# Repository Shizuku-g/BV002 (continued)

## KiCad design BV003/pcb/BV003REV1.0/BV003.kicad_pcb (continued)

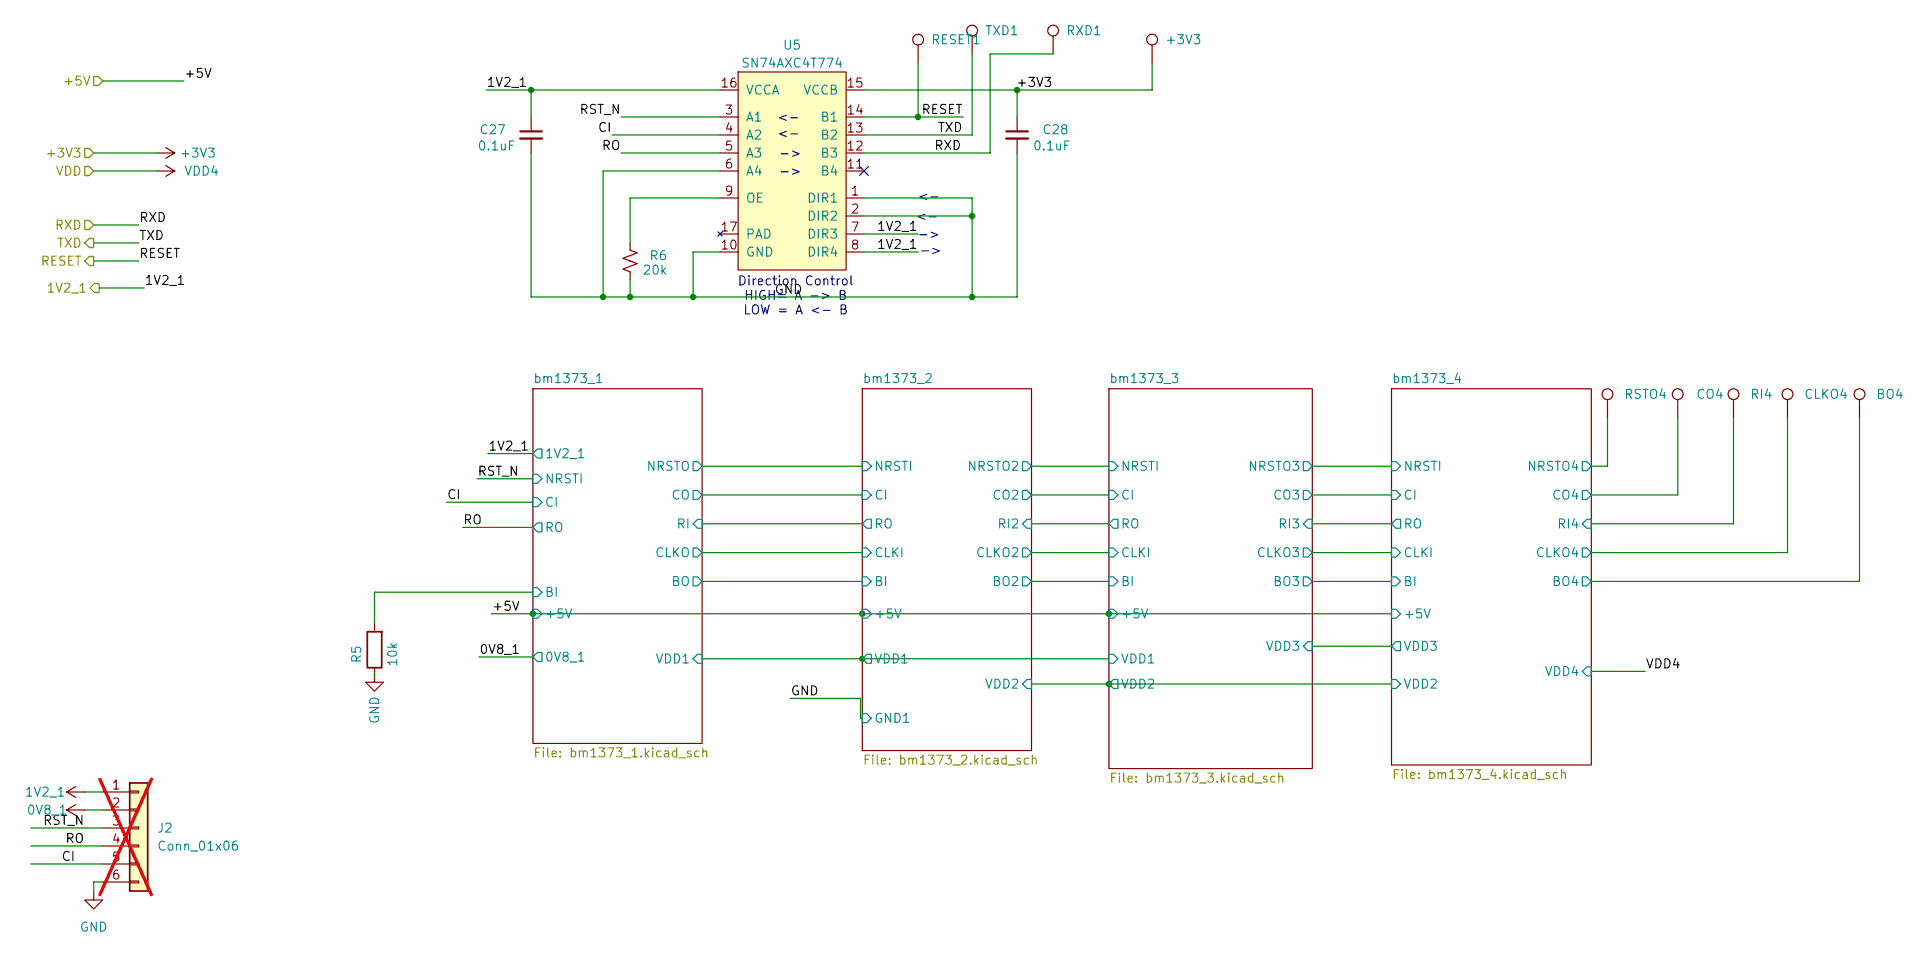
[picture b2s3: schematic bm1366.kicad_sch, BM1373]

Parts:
+3V3: TestPoint_Pad_D1.5mm
BO4: TestPoint_Pad_D1.5mm
C27, C28: 0.1uF; C_0402_1005Metric; PARTNO KGM05AR71C104KH
CLKO4: TestPoint_Pad_D1.5mm
CO4: TestPoint_Pad_D1.5mm
J2: Conn_01x06; PinHeader_1x06_P1.27mm_Vertical; not fitted
R5: 10k; R_0402_1005Metric; LCSC C140868
R6: 20k; R_0402_1005Metric; PARTNO RC0402FR-0720KL
RESET1: TestPoint_Pad_D1.5mm
RI4: TestPoint_Pad_D1.5mm
RSTO4: TestPoint_Pad_D1.5mm
RXD1: TestPoint_Pad_D1.5mm
TXD1: TestPoint_Pad_D1.5mm
U5: SN74AXC4T774; TSSOP-16_4.4x5mm_P0.65mm; PARTNO SN74AXC4T774BQBR

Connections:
1V2_1: C27.1, J2.1, U5.7 (DIR3), U5.8 (DIR4), U5.16 (VCCA); also elsewhere on the board
+0V8_1: J2.2; also elsewhere on the board
+3V3: +3V3.1 (1_1), C28.1, U5.15 (VCCB); also elsewhere on the board
/BM1370/CI: J2.5, U5.4 (A2); also elsewhere on the board
/BM1370/RESET: RESET1.1 (1_1), U5.14 (B1); also elsewhere on the board
/BM1370/RO: J2.4, U5.5 (A3); also elsewhere on the board
/BM1370/RST_N: J2.3, U5.3 (A1); also elsewhere on the board
/BM1370/RXD: RXD1.1 (1_1), U5.12 (B3); also elsewhere on the board
/BM1370/TXD: TXD1.1 (1_1), U5.13 (B2); also elsewhere on the board
/BM1370/bm1373_1/BI: R5.2; also elsewhere on the board
/BM1370/bm1373_4/BO: BO4.1 (1_1); also elsewhere on the board
/BM1370/bm1373_4/CLKO4: CLKO4.1 (1_1); also elsewhere on the board
/BM1370/bm1373_4/CO: CO4.1 (1_1); also elsewhere on the board
/BM1370/bm1373_4/RI: RI4.1 (1_1); also elsewhere on the board
/BM1370/bm1373_4/RSTO: RSTO4.1 (1_1); also elsewhere on the board
GND: C27.2, C28.2, J2.6, R5.1, R6.1, U5.1 (DIR1), U5.2 (DIR2), U5.6 (A4), U5.10 (GND); also elsewhere on the board
unnamed: R6.2, U5.9 (OE)

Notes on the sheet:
Direction Control HIGH= A -> B LOW = A <- B

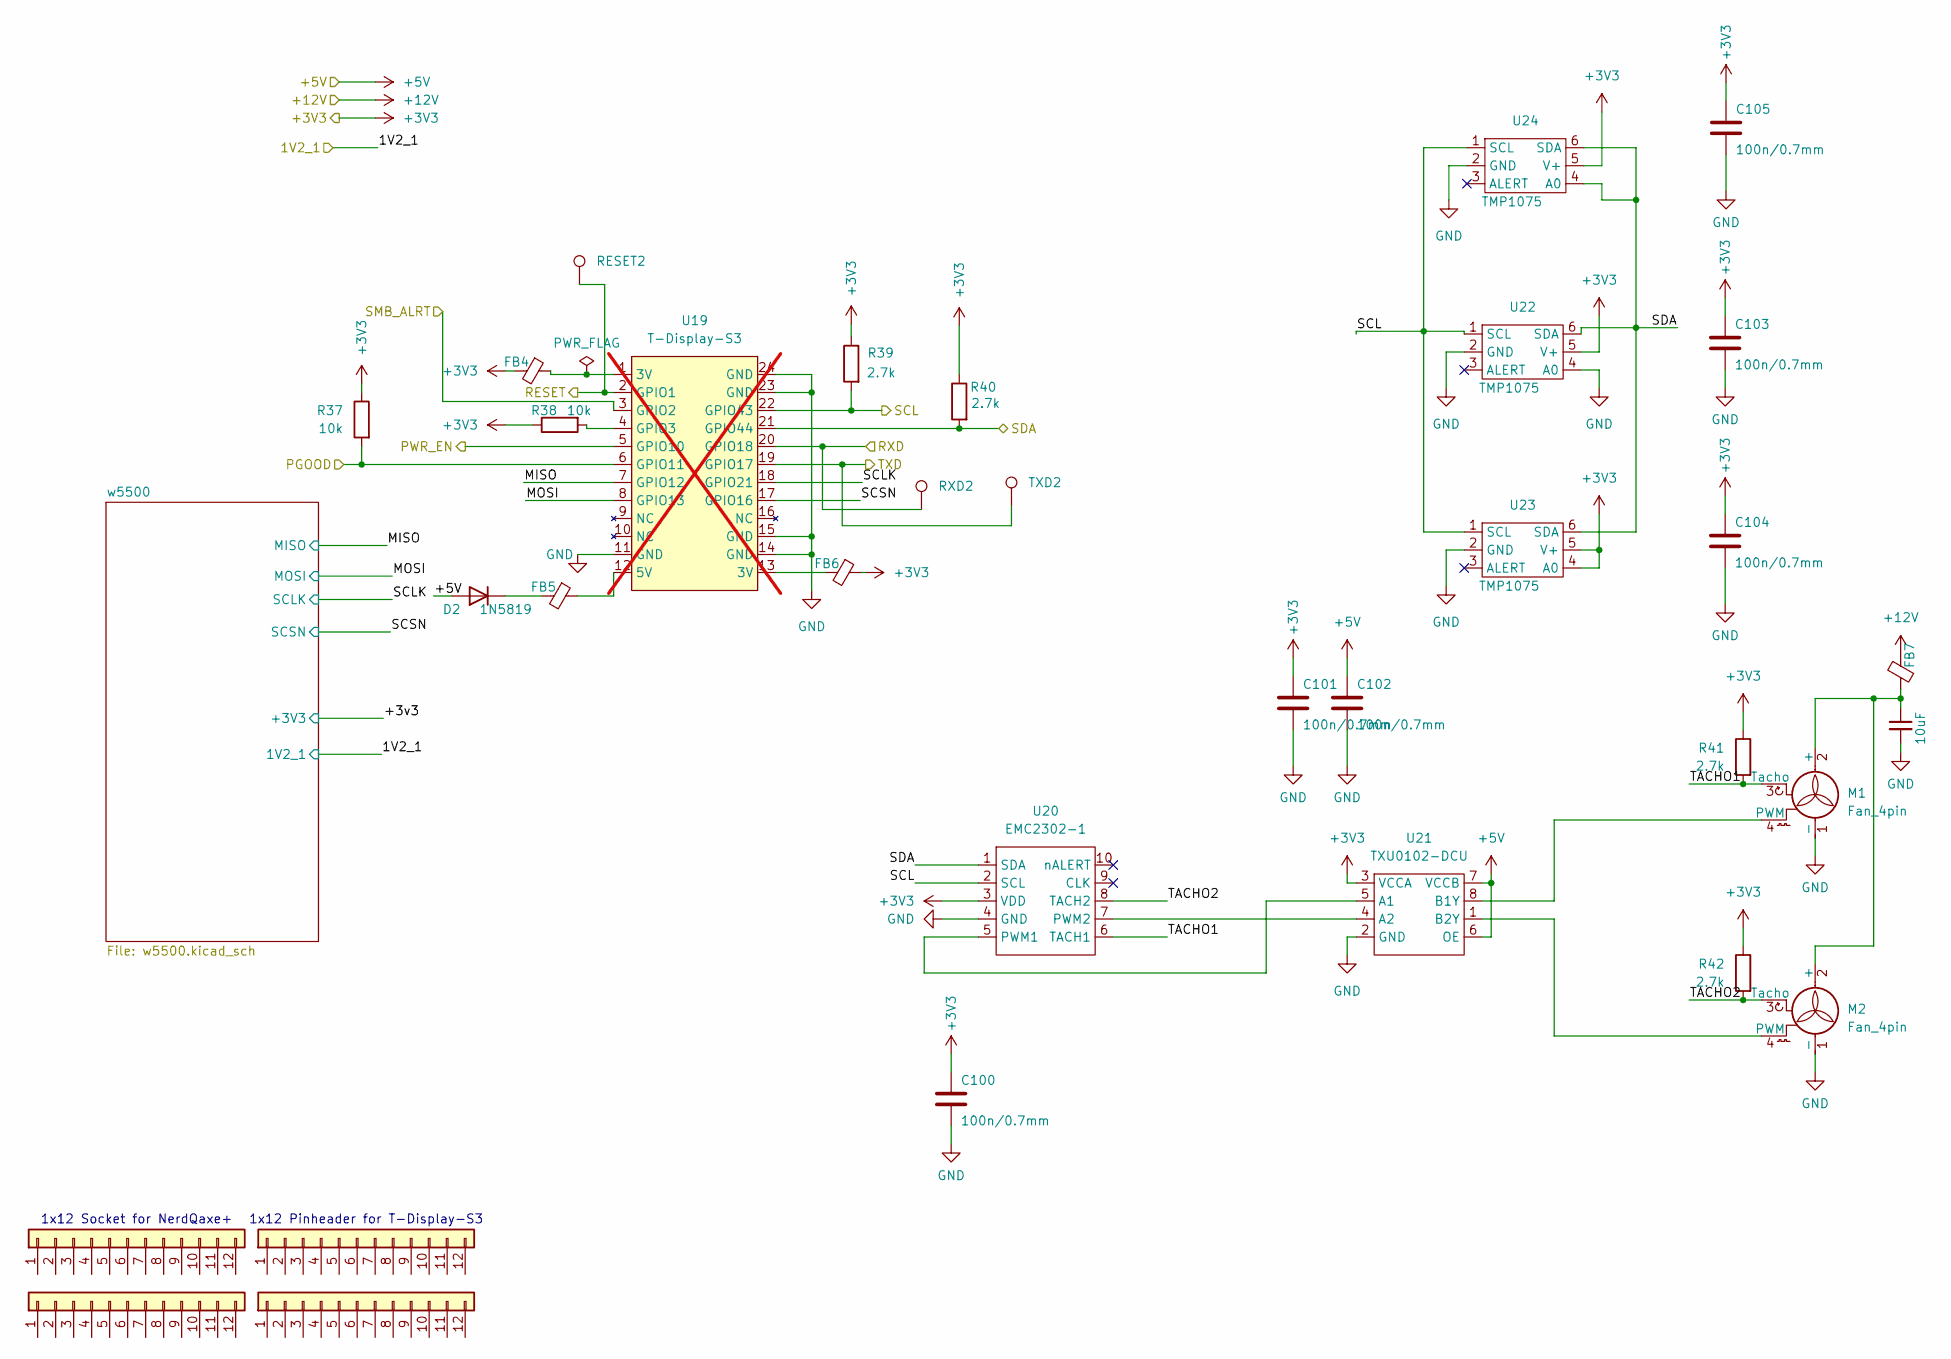
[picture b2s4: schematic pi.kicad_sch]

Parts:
C100, C101, C102, C103, C104, C105: 100n/0.7mm; C_0805_2012Metric; LCSC C519981
C106: 10uF; C_0603_1608Metric; PARTNO CL10A106MO8NQNC; LCSC C92487
D2: 1N5819; D_SMA; PARTNO C460770; LCSC C460770
FB4, FB5, FB6, FB7: BLM21PG221SN1D; R_0805_2012Metric; LCSC C85840
J3, J4: Conn_01x12-Socket
J5, J6: Conn_01x12-Header
M1, M2: Fan_4pin; FanPinHeader_1x04_P2.54mm_Vertical; LCSC C240840
R37, R38: 10k; R_0805_2012Metric; LCSC C140868
R39, R40, R41, R42: 2.7k; R_0805_2012Metric; LCSC C17530
RESET2: TestPoint_Pad_D1.5mm
RXD2: TestPoint_Pad_D1.5mm
TXD2: TestPoint_Pad_D1.5mm
U19: T-Display-S3; not fitted
U20: EMC2302-1; MSOP-10_3x3mm_P0.5mm; LCSC C626969
U21: TXU0102-DCU; VSSOP-8_2.3x2mm_P0.5mm; LCSC C5217871
U22, U23, U24: TMP1075; TMP1075-DRL; LCSC C3663690

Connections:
+3V3: C100.1, C101.1, C103.1, C104.1, C105.1, FB4.2, FB6.1, R37.1, R38.1, R39.1, R40.1, R40.2, R41.1, R42.1, U19.21 (GPIO44), U20.1 (SDA), U20.3 (VDD), U21.3 (VCCA), U22.5 (V+), U22.6 (SDA), U23.4 (A0), U23.5 (V+), U23.6 (SDA), U24.4 (A0), U24.5 (V+), U24.6 (SDA); also elsewhere on the board
+5V: C102.1, D2.2 (A), U21.6 (OE), U21.7 (VCCB); also elsewhere on the board
/BM1370/RESET: RESET2.1 (1_1), U19.2 (GPIO1); also elsewhere on the board
/BM1370/RXD: RXD2.1 (1_1), U19.20 (GPIO18); also elsewhere on the board
/BM1370/TXD: TXD2.1 (1_1), U19.19 (GPIO17); also elsewhere on the board
/T-Display-S3/MISO: U19.7 (GPIO12); also elsewhere on the board
/T-Display-S3/MOSI: U19.8 (GPIO13); also elsewhere on the board
/T-Display-S3/SCL: R39.2, U19.22 (GPIO43), U20.2 (SCL), U22.1 (SCL), U23.1 (SCL), U24.1 (SCL); also elsewhere on the board
/T-Display-S3/SCLK: U19.18 (GPIO21); also elsewhere on the board
/T-Display-S3/SCSN: U19.17 (GPIO16); also elsewhere on the board
/T-Display-S3/SMB_ALRT: U19.3 (GPIO2); also elsewhere on the board
/T-Display-S3/TACHO1: M1.3 (Tacho), R41.2, U20.6 (TACH1)
/T-Display-S3/TACHO2: M2.3 (Tacho), R42.2, U20.8 (TACH2)
/power1/PWR_EN: U19.5 (GPIO10); also elsewhere on the board
GND: C100.2, C101.2, C102.2, C103.2, C104.2, C105.2, C106.2, M1.1 (-), M2.1 (-), U19.11 (GND), U19.14 (GND), U19.15 (GND), U19.23 (GND), U19.24 (GND), U20.4 (GND), U21.2 (GND), U22.2 (GND), U22.4 (A0), U23.2 (GND), U24.2 (GND); also elsewhere on the board
unnamed: D2.1 (K), FB5.2
unnamed: FB4.1, U19.1 (3V)
unnamed: FB6.2, U19.13 (3V)
unnamed: C106.1, FB7.1, M1.2 (+), M2.2 (+)
unnamed: M1.4 (PWM), U21.8 (B1Y)
unnamed: M2.4 (PWM), U21.1 (B2Y)
unnamed: FB5.1, U19.12 (5V)
unnamed: R38.2, U19.4 (GPIO3)
unnamed: U20.5 (PWM1), U21.5 (A1)
unnamed: U20.7 (PWM2), U21.4 (A2)
PGOOD: R37.2, U19.6 (GPIO11); also elsewhere on the board

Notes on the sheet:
1x12 Socket for NerdQaxe+
1x12 Pinheader for T-Display-S3

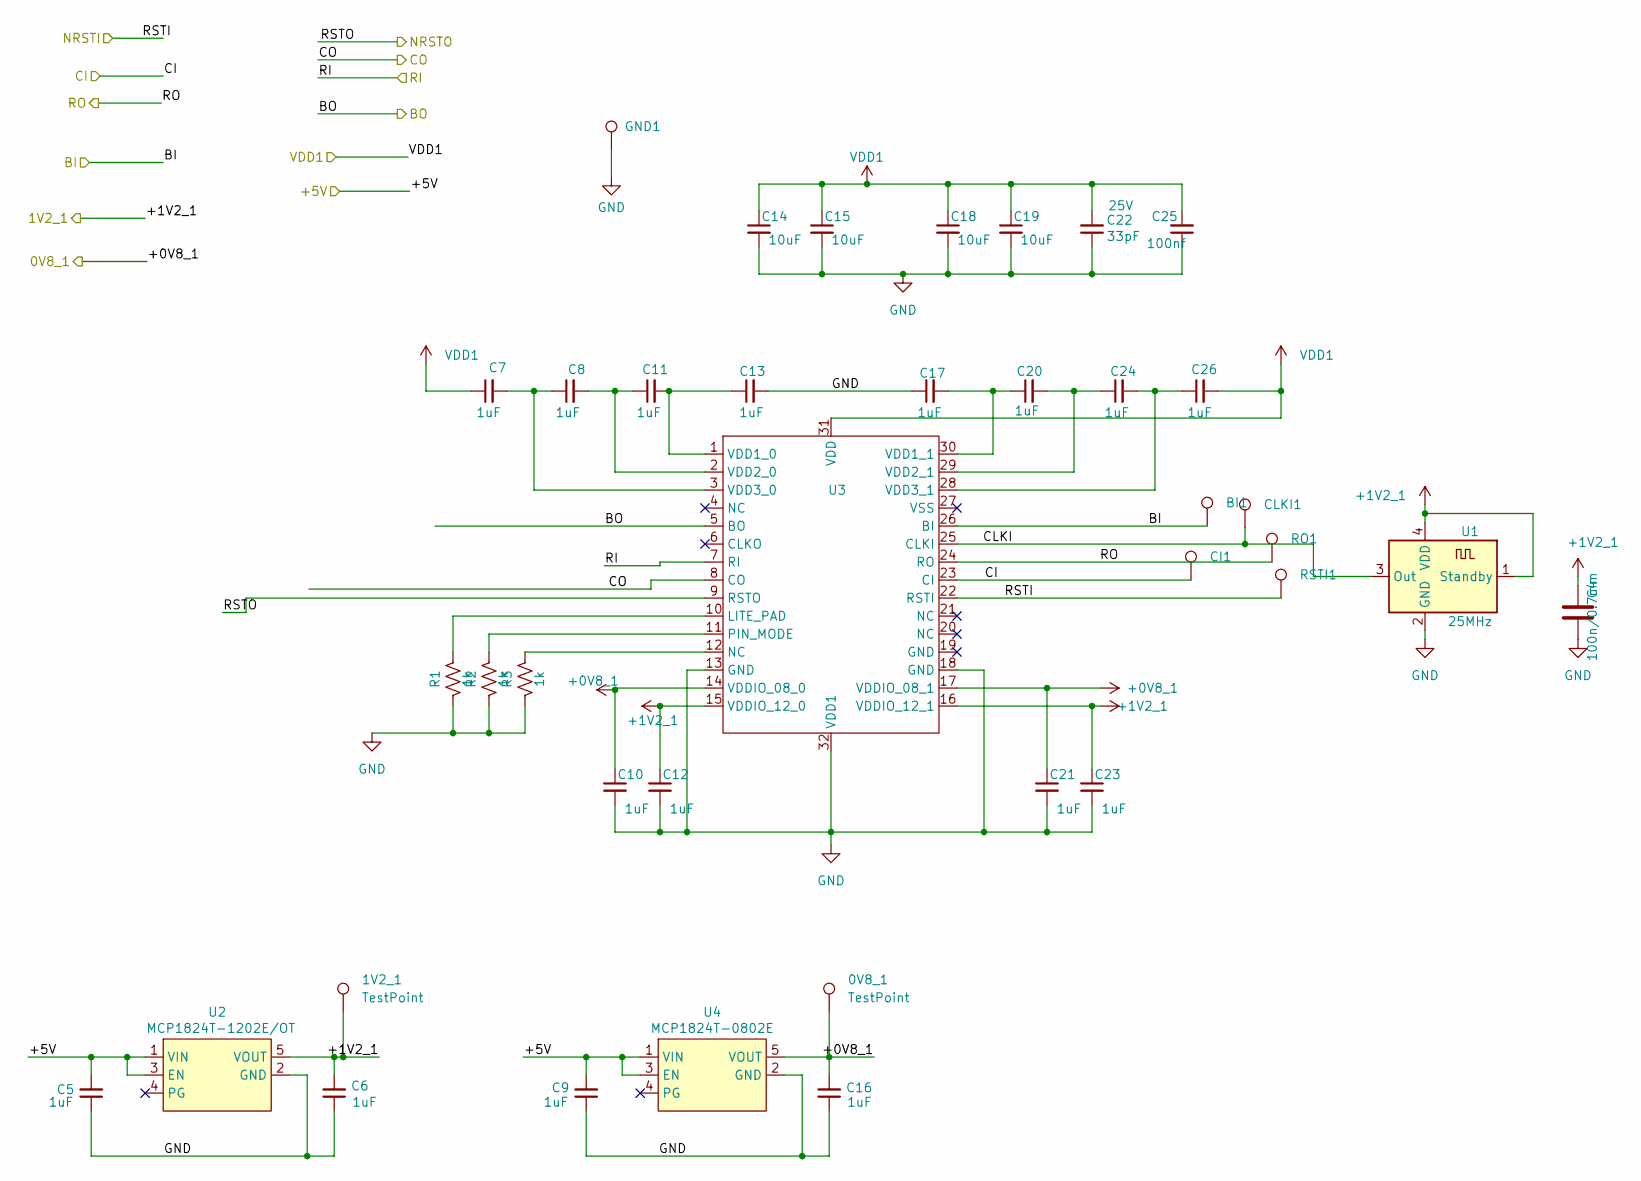
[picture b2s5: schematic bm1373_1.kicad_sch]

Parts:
0V8_1, 1V2_1: TestPoint; TestPoint_Pad_D1.5mm
BI1: TestPoint_Pad_D1.5mm
C4: 100n/0.7mm; C_0805_2012Metric; LCSC C519981
C5, C6, C9, C16: 1uF; C_0402_1005Metric; PARTNO EMK105BJ105MV-F
C7, C8, C10, C11, C12, C13, C17, C20, C21, C23, C24, C26: 1uF; C_0402_1005Metric; PARTNO CL05A105KO5NNNC; LCSC C29266
C14, C15, C18, C19: 10uF; C_0603_1608Metric; PARTNO CL10A106MO8NQNC; LCSC C92487 Hot
C22: 33pF; C_0402_1005Metric; Voltage 25V; PARTNO KGM05ACG1E330JH
C25: 100nf; C_0402_1005Metric; PARTNO GRM188R61E106KA73D
CI1: TestPoint_Pad_D1.5mm
CLKI1: TestPoint_Pad_D1.5mm
GND1: TestPoint_Pad_D1.5mm
R1, R2, R3: 1k; R_0402_1005Metric; PARTNO RC0402FR-071KL; LCSC C106235
RO1: TestPoint_Pad_D1.5mm
RSTI1: TestPoint_Pad_D1.5mm
U1: 25MHz; Oscillator_SMD_Abracon_ASDMB-4Pin_2.5x2.0mm; LCSC C5137262
U2: MCP1824T-1202E/OT; SOT-23-5; PARTNO MCP1824T-1202E/OT
U3: B1373CC
U4: MCP1824T-0802E; SOT-23-5; PARTNO MCP1824T-0802E/OT

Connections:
1V2_1: 1V2_1.1 (1_1), C4.1, C6.2, C12.1, C23.1, U1.1 (Standby), U1.4 (VDD), U2.5 (VOUT), U3.15 (VDDIO_12_0), U3.16 (VDDIO_12_1); also elsewhere on the board
+0V8_1: 0V8_1.1 (1_1), C10.1, C16.2, C21.1, U3.14 (VDDIO_08_0), U3.17 (VDDIO_08_1), U4.5 (VOUT); also elsewhere on the board
+5V: C5.2, C9.2, U2.1 (VIN), U2.3 (EN), U4.1 (VIN), U4.3 (EN); also elsewhere on the board
/BM1370/CI: CI1.1 (1_1), U3.23 (CI); also elsewhere on the board
/BM1370/RO: RO1.1 (1_1), U3.24 (RO); also elsewhere on the board
/BM1370/RST_N: RSTI1.1 (1_1), U3.22 (RSTI); also elsewhere on the board
/BM1370/bm1373_1/BI: BI1.1 (1_1), U3.26 (BI); also elsewhere on the board
/BM1370/bm1373_1/BO: U3.5 (BO); also elsewhere on the board
/BM1370/bm1373_1/CLKI: CLKI1.1 (1_1), U1.3 (Out), U3.25 (CLKI)
/BM1370/bm1373_1/CO: U3.8 (CO); also elsewhere on the board
/BM1370/bm1373_1/RI: U3.7 (RI); also elsewhere on the board
/BM1370/bm1373_1/RSTO: U3.9 (RSTO); also elsewhere on the board
GND: C4.2, C5.1, C6.1, C9.1, C10.2, C12.2, C13.2, C14.2, C15.2, C16.1, C17.1, C18.2, C19.2, C21.2, C22.1, C23.2, C25.1, GND1.1 (1_1), R1.2, R2.2, R3.2, U1.2 (GND), U2.2 (GND), U3.13 (GND), U3.18 (GND), U3.19 (GND), U3.32 (VDD1), U4.2 (GND); also elsewhere on the board
unnamed: R3.1, U3.12 (NC)
unnamed 110: U3.6 (CLKO); also elsewhere on the board
unnamed: R1.1, U3.10 (LITE_PAD)
unnamed: R2.1, U3.11 (PIN_MODE)
unnamed: C11.2, C13.1, U3.1 (VDD1_0)
unnamed: C17.2, C20.1, U3.30 (VDD1_1)
unnamed: C8.2, C11.1, U3.2 (VDD2_0)
unnamed: C20.2, C24.1, U3.29 (VDD2_1)
unnamed: C7.2, C8.1, U3.3 (VDD3_0)
unnamed: C24.2, C26.1, U3.28 (VDD3_1)
VDD1: C7.1, C14.1, C15.1, C18.1, C19.1, C22.2, C25.2, C26.2, U3.31 (VDD); also elsewhere on the board

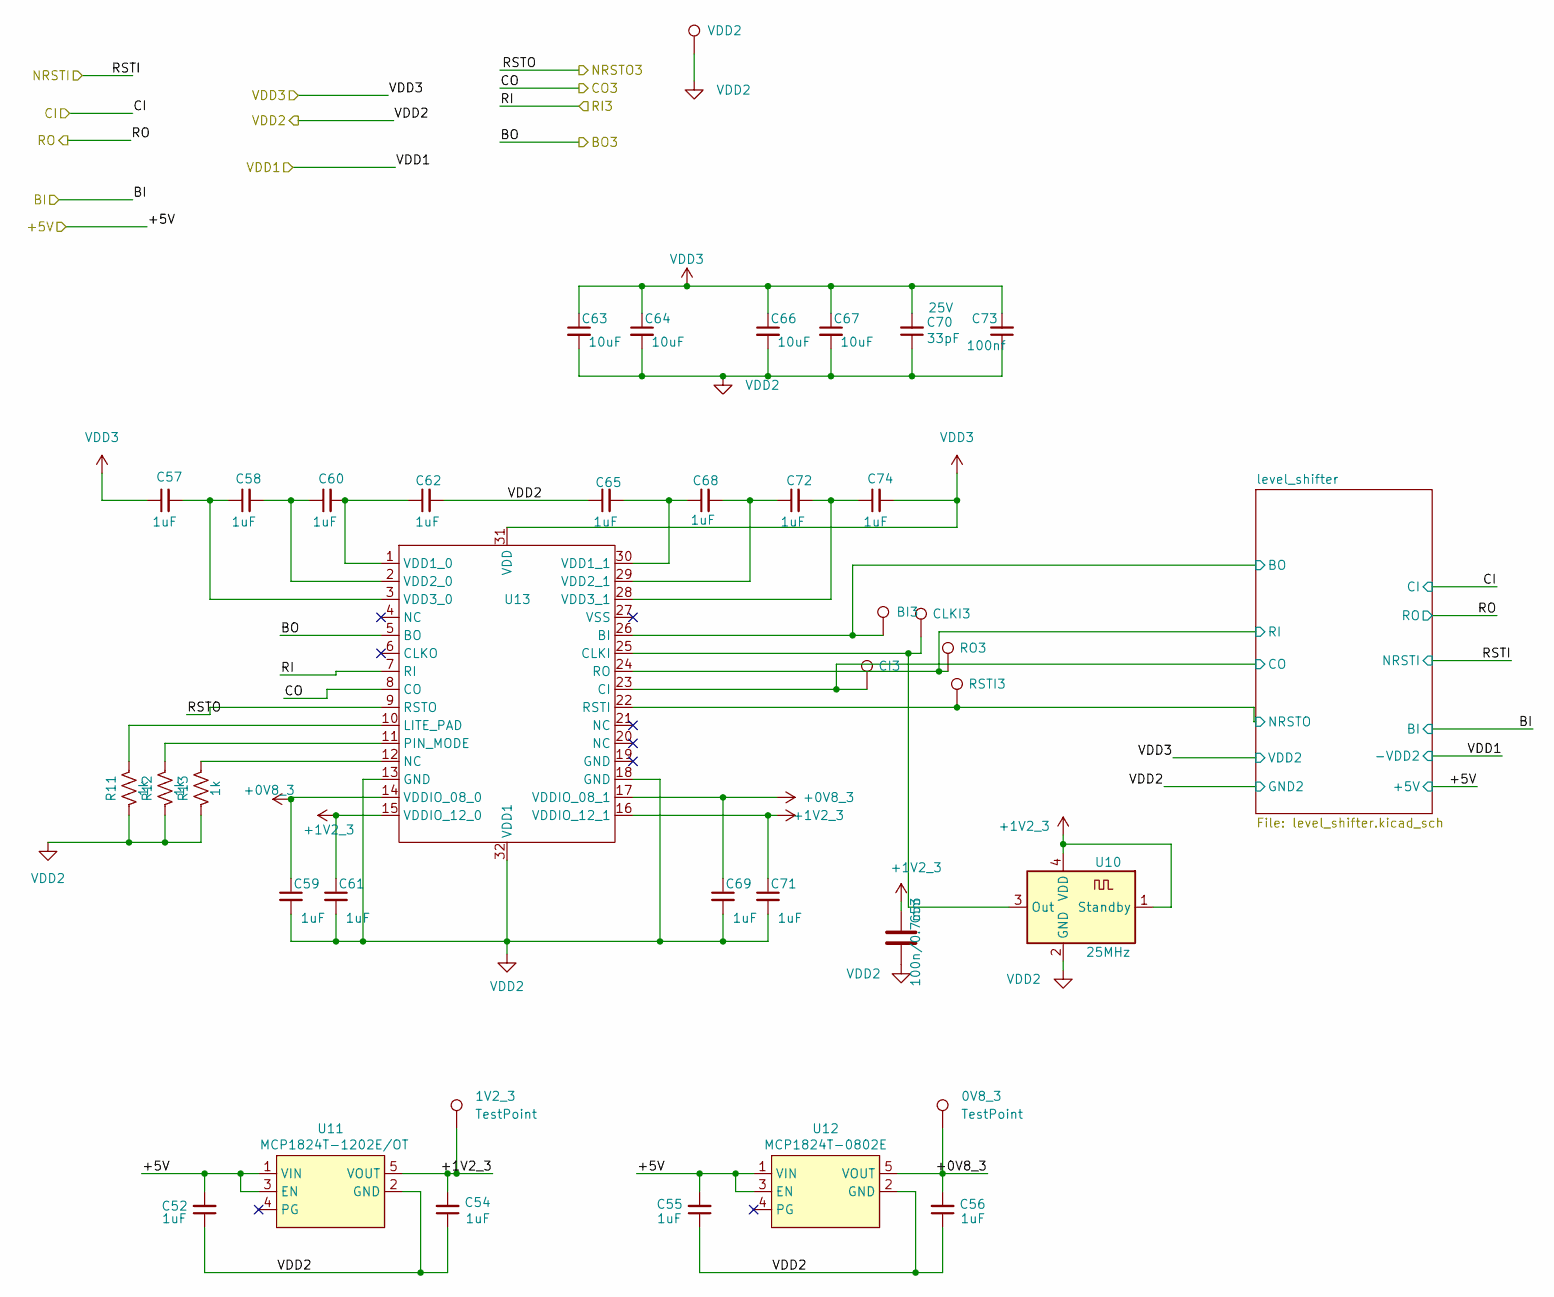
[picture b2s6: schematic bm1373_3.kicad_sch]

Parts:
0V8_3, 1V2_3: TestPoint; TestPoint_Pad_D1.5mm
BI3: TestPoint_Pad_D1.5mm
C52, C54, C55, C56: 1uF; C_0402_1005Metric; PARTNO EMK105BJ105MV-F
C53: 100n/0.7mm; C_0805_2012Metric; LCSC C519981
C57, C58, C59, C60, C61, C62, C65, C68, C69, C71, C72, C74: 1uF; C_0402_1005Metric; PARTNO CL05A105KO5NNNC; LCSC C29266
C63, C64, C66, C67: 10uF; C_0603_1608Metric; PARTNO CL10A106MO8NQNC; LCSC C92487 Hot
C70: 33pF; C_0402_1005Metric; Voltage 25V; PARTNO KGM05ACG1E330JH
C73: 100nf; C_0402_1005Metric; PARTNO GRM188R61E106KA73D
CI3: TestPoint_Pad_D1.5mm
CLKI3: TestPoint_Pad_D1.5mm
R11, R12, R13: 1k; R_0402_1005Metric; PARTNO RC0402FR-071KL; LCSC C106235
RO3: TestPoint_Pad_D1.5mm
RSTI3: TestPoint_Pad_D1.5mm
U10: 25MHz; Oscillator_SMD_Abracon_ASDMB-4Pin_2.5x2.0mm; LCSC C5137262
U11: MCP1824T-1202E/OT; SOT-23-5; PARTNO MCP1824T-1202E/OT
U12: MCP1824T-0802E; SOT-23-5; PARTNO MCP1824T-0802E/OT
U13: B1373CC
VDD2: TestPoint_Pad_D1.5mm

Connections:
+0V8_3: 0V8_3.1 (1_1), C56.2, C59.1, C69.1, U12.5 (VOUT), U13.14 (VDDIO_08_0), U13.17 (VDDIO_08_1)
+1V2_3: 1V2_3.1 (1_1), C53.1, C54.2, C61.1, C71.1, U10.1 (Standby), U10.4 (VDD), U11.5 (VOUT), U13.15 (VDDIO_12_0), U13.16 (VDDIO_12_1)
+5V: C52.2, C55.2, U11.1 (VIN), U11.3 (EN), U12.1 (VIN), U12.3 (EN); also elsewhere on the board
/BM1370/bm1373_3/BO: U13.5 (BO); also elsewhere on the board
/BM1370/bm1373_3/CO: U13.8 (CO); also elsewhere on the board
/BM1370/bm1373_3/RI: U13.7 (RI); also elsewhere on the board
/BM1370/bm1373_3/RSTO: U13.9 (RSTO); also elsewhere on the board
/BM1370/bm1373_3/level_shifter/BI2: BI3.1 (1_1), U13.26 (BI); also elsewhere on the board
/BM1370/bm1373_3/level_shifter/CI2: CI3.1 (1_1), U13.23 (CI); also elsewhere on the board
/BM1370/bm1373_3/level_shifter/NRSTI2: RSTI3.1 (1_1), U13.22 (RSTI); also elsewhere on the board
/BM1370/bm1373_3/level_shifter/RO2: RO3.1 (1_1), U13.24 (RO); also elsewhere on the board
unnamed: R13.1, U13.12 (NC)
unnamed: CLKI3.1 (1_1), U10.3 (Out), U13.25 (CLKI)
unnamed 131: U13.6 (CLKO); also elsewhere on the board
unnamed: R11.1, U13.10 (LITE_PAD)
unnamed: R12.1, U13.11 (PIN_MODE)
unnamed: C60.2, C62.1, U13.1 (VDD1_0)
unnamed: C65.2, C68.1, U13.30 (VDD1_1)
unnamed: C58.2, C60.1, U13.2 (VDD2_0)
unnamed: C68.2, C72.1, U13.29 (VDD2_1)
unnamed: C57.2, C58.1, U13.3 (VDD3_0)
unnamed: C72.2, C74.1, U13.28 (VDD3_1)
VDD2: C52.1, C53.2, C54.1, C55.1, C56.1, C59.2, C61.2, C62.2, C63.2, C64.2, C65.1, C66.2, C67.2, C69.2, C70.1, C71.2, C73.1, R11.2, R12.2, R13.2, U10.2 (GND), U11.2 (GND), U12.2 (GND), U13.13 (GND), U13.18 (GND), U13.19 (GND), U13.32 (VDD1), VDD2.1 (1_1); also elsewhere on the board
VDD3: C57.1, C63.1, C64.1, C66.1, C67.1, C70.2, C73.2, C74.2, U13.31 (VDD); also elsewhere on the board

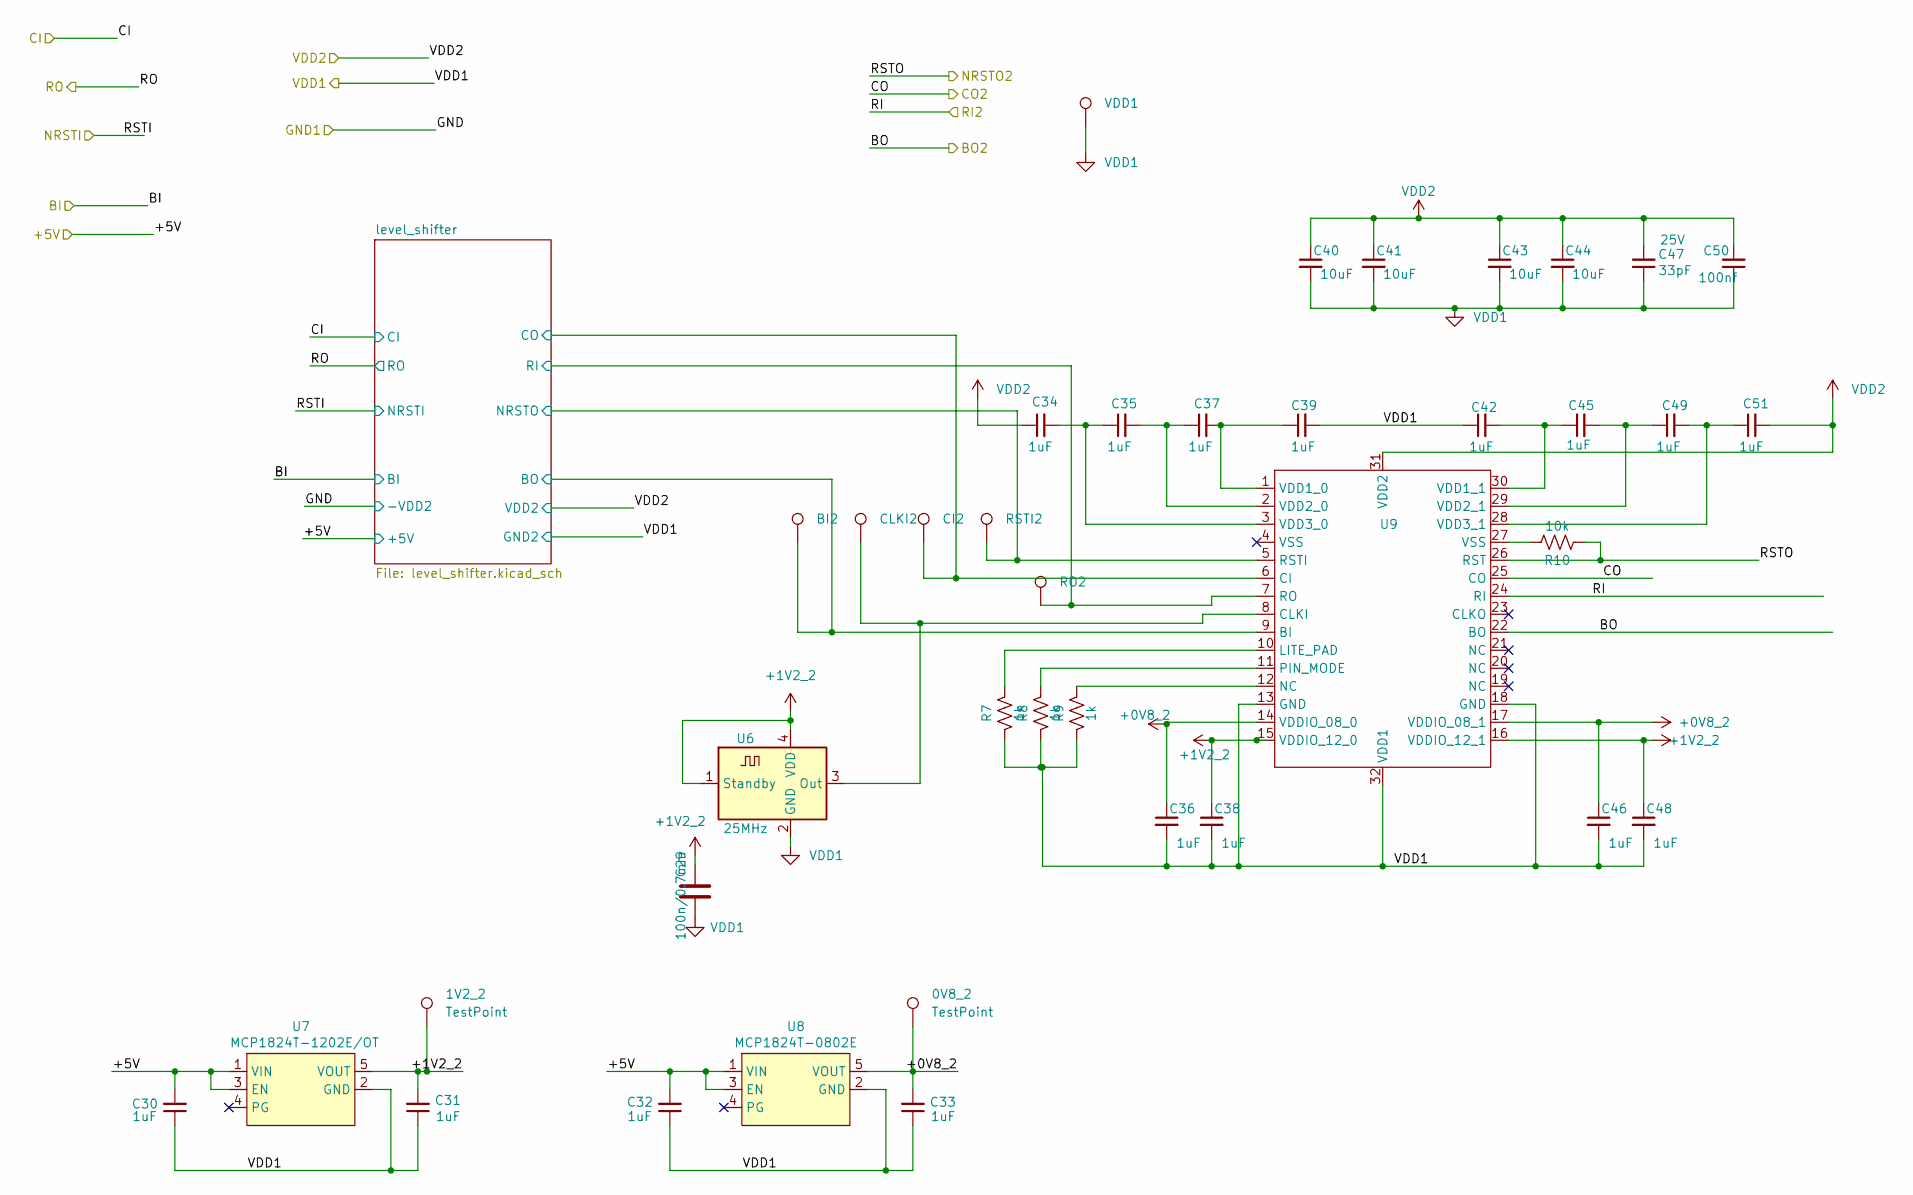
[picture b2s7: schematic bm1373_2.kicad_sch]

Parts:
0V8_2, 1V2_2: TestPoint; TestPoint_Pad_D1.5mm
BI2: TestPoint_Pad_D1.5mm
C29: 100n/0.7mm; C_0805_2012Metric; LCSC C519981
C30, C31, C32, C33: 1uF; C_0402_1005Metric; PARTNO EMK105BJ105MV-F
C34, C35, C36, C37, C38, C39, C42, C45, C46, C48, C49, C51: 1uF; C_0402_1005Metric; PARTNO CL05A105KO5NNNC; LCSC C29266
C40, C41, C43, C44: 10uF; C_0603_1608Metric; PARTNO CL10A106MO8NQNC; LCSC C92487 Hot
C47: 33pF; C_0402_1005Metric; Voltage 25V; PARTNO KGM05ACG1E330JH
C50: 100nf; C_0402_1005Metric; PARTNO GRM188R61E106KA73D
CI2: TestPoint_Pad_D1.5mm
CLKI2: TestPoint_Pad_D1.5mm
R7, R8, R9: 1k; R_0402_1005Metric; PARTNO RC0402FR-071KL; LCSC C106235
R10: 10k; R_0402_1005Metric; PARTNO RC0402DR-0710KL; LCSC C471764
RO2: TestPoint_Pad_D1.5mm
RSTI2: TestPoint_Pad_D1.5mm
U6: 25MHz; Oscillator_SMD_Abracon_ASDMB-4Pin_2.5x2.0mm; LCSC C5137262
U7: MCP1824T-1202E/OT; SOT-23-5; PARTNO MCP1824T-1202E/OT
U8: MCP1824T-0802E; SOT-23-5; PARTNO MCP1824T-0802E/OT
U9: B1373CC
VDD1: TestPoint_Pad_D1.5mm

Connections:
+0V8_2: 0V8_2.1 (1_1), C33.2, C36.1, C46.1, U8.5 (VOUT), U9.14 (VDDIO_08_0), U9.17 (VDDIO_08_1)
+1V2_2: 1V2_2.1 (1_1), C29.1, C31.2, C38.1, C48.1, U6.1 (Standby), U6.4 (VDD), U7.5 (VOUT), U9.15 (VDDIO_12_0), U9.16 (VDDIO_12_1)
+5V: C30.2, C32.2, U7.1 (VIN), U7.3 (EN), U8.1 (VIN), U8.3 (EN); also elsewhere on the board
/BM1370/bm1373_2/BO: U9.22 (BO); also elsewhere on the board
/BM1370/bm1373_2/CO: U9.25 (CO); also elsewhere on the board
/BM1370/bm1373_2/RI: U9.24 (RI); also elsewhere on the board
/BM1370/bm1373_2/RSTO: R10.1, U9.26 (RST); also elsewhere on the board
/BM1370/bm1373_2/level_shifter/BI2: BI2.1 (1_1), U9.9 (BI); also elsewhere on the board
/BM1370/bm1373_2/level_shifter/CI2: CI2.1 (1_1), U9.6 (CI); also elsewhere on the board
/BM1370/bm1373_2/level_shifter/NRSTI2: RSTI2.1 (1_1), U9.5 (RSTI); also elsewhere on the board
/BM1370/bm1373_2/level_shifter/RO2: RO2.1 (1_1), U9.7 (RO); also elsewhere on the board
unnamed: R9.1, U9.12 (NC)
unnamed: R10.2, U9.27 (VSS)
unnamed: CLKI2.1 (1_1), U6.3 (Out), U9.8 (CLKI)
unnamed 121: U9.23 (CLKO); also elsewhere on the board
unnamed: R7.1, U9.10 (LITE_PAD)
unnamed: R8.1, U9.11 (PIN_MODE)
unnamed: C37.2, C39.1, U9.1 (VDD1_0)
unnamed: C42.2, C45.1, U9.30 (VDD1_1)
unnamed: C35.2, C37.1, U9.2 (VDD2_0)
unnamed: C45.2, C49.1, U9.29 (VDD2_1)
unnamed: C34.2, C35.1, U9.3 (VDD3_0)
unnamed: C49.2, C51.1, U9.28 (VDD3_1)
VDD1: C29.2, C30.1, C31.1, C32.1, C33.1, C36.2, C38.2, C39.2, C40.2, C41.2, C42.1, C43.2, C44.2, C46.2, C47.1, C48.2, C50.1, R7.2, R8.2, R9.2, U6.2 (GND), U7.2 (GND), U8.2 (GND), U9.13 (GND), U9.18 (GND), U9.32 (VDD1), VDD1.1 (1_1); also elsewhere on the board
VDD2: C34.1, C40.1, C41.1, C43.1, C44.1, C47.2, C50.2, C51.2, U9.31 (VDD2); also elsewhere on the board

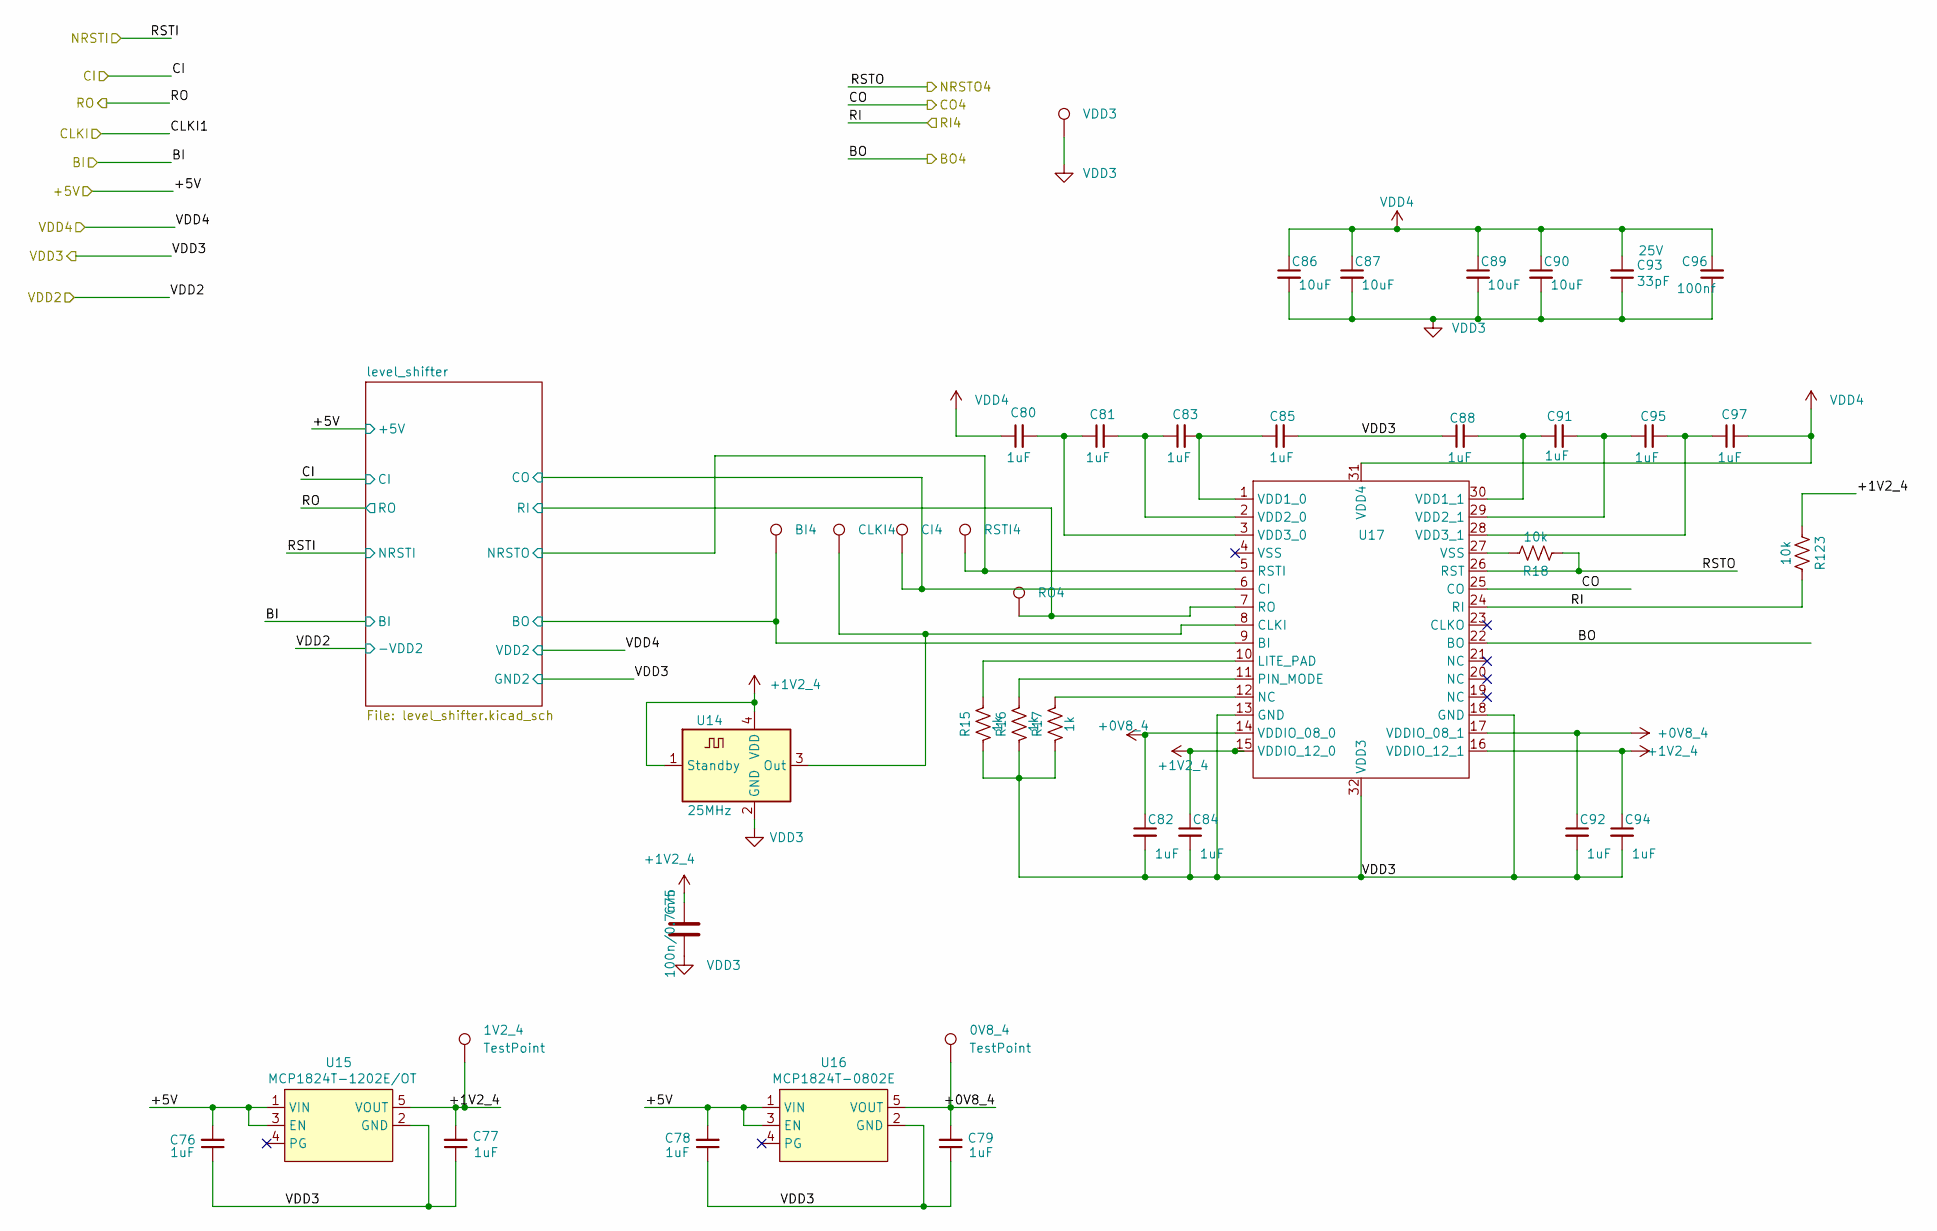
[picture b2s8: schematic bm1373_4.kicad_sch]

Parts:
0V8_4, 1V2_4: TestPoint; TestPoint_Pad_D1.5mm
BI4: TestPoint_Pad_D1.5mm
C75: 100n/0.7mm; C_0805_2012Metric; LCSC C519981
C76, C77, C78, C79: 1uF; C_0402_1005Metric; PARTNO EMK105BJ105MV-F
C80, C81, C82, C83, C84, C85, C88, C91, C92, C94, C95, C97: 1uF; C_0402_1005Metric; PARTNO CL05A105KO5NNNC; LCSC C29266
C86, C87, C89, C90: 10uF; C_0603_1608Metric; PARTNO CL10A106MO8NQNC; LCSC C92487 Hot
C93: 33pF; C_0402_1005Metric; Voltage 25V; PARTNO KGM05ACG1E330JH
C96: 100nf; C_0402_1005Metric; PARTNO GRM188R61E106KA73D
CI4: TestPoint_Pad_D1.5mm
CLKI4: TestPoint_Pad_D1.5mm
R15, R16, R17: 1k; R_0402_1005Metric; PARTNO RC0402FR-071KL; LCSC C106235
R18, R123: 10k; R_0402_1005Metric; PARTNO RC0402DR-0710KL; LCSC C471764
RO4: TestPoint_Pad_D1.5mm
RSTI4: TestPoint_Pad_D1.5mm
U14: 25MHz; Oscillator_SMD_Abracon_ASDMB-4Pin_2.5x2.0mm; LCSC C5137262
U15: MCP1824T-1202E/OT; SOT-23-5; PARTNO MCP1824T-1202E/OT
U16: MCP1824T-0802E; SOT-23-5; PARTNO MCP1824T-0802E/OT
U17: B1373CC
VDD3: TestPoint_Pad_D1.5mm

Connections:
+0V8_4: 0V8_4.1 (1_1), C79.2, C82.1, C92.1, U16.5 (VOUT), U17.14 (VDDIO_08_0), U17.17 (VDDIO_08_1)
+1V2_4: 1V2_4.1 (1_1), C75.1, C77.2, C84.1, C94.1, R123.1, U14.1 (Standby), U14.4 (VDD), U15.5 (VOUT), U17.15 (VDDIO_12_0), U17.16 (VDDIO_12_1)
+5V: C76.2, C78.2, U15.1 (VIN), U15.3 (EN), U16.1 (VIN), U16.3 (EN); also elsewhere on the board
/BM1370/bm1373_4/BO: U17.22 (BO); also elsewhere on the board
/BM1370/bm1373_4/CLKO4: U17.23 (CLKO); also elsewhere on the board
/BM1370/bm1373_4/CO: U17.25 (CO); also elsewhere on the board
/BM1370/bm1373_4/RI: R123.2, U17.24 (RI); also elsewhere on the board
/BM1370/bm1373_4/RSTO: R18.1, U17.26 (RST); also elsewhere on the board
/BM1370/bm1373_4/level_shifter/BI2: BI4.1 (1_1), U17.9 (BI); also elsewhere on the board
/BM1370/bm1373_4/level_shifter/CI2: CI4.1 (1_1), U17.6 (CI); also elsewhere on the board
/BM1370/bm1373_4/level_shifter/NRSTI2: RSTI4.1 (1_1), U17.5 (RSTI); also elsewhere on the board
/BM1370/bm1373_4/level_shifter/RO2: RO4.1 (1_1), U17.7 (RO); also elsewhere on the board
unnamed: R17.1, U17.12 (NC)
unnamed: R18.2, U17.27 (VSS)
unnamed: CLKI4.1 (1_1), U14.3 (Out), U17.8 (CLKI)
unnamed: R15.1, U17.10 (LITE_PAD)
unnamed: R16.1, U17.11 (PIN_MODE)
unnamed: C83.2, C85.1, U17.1 (VDD1_0)
unnamed: C88.2, C91.1, U17.30 (VDD1_1)
unnamed: C81.2, C83.1, U17.2 (VDD2_0)
unnamed: C91.2, C95.1, U17.29 (VDD2_1)
unnamed: C80.2, C81.1, U17.3 (VDD3_0)
unnamed: C95.2, C97.1, U17.28 (VDD3_1)
VDD: C80.1, C86.1, C87.1, C89.1, C90.1, C93.2, C96.2, C97.2, U17.31 (VDD4); also elsewhere on the board
VDD3: C75.2, C76.1, C77.1, C78.1, C79.1, C82.2, C84.2, C85.2, C86.2, C87.2, C88.1, C89.2, C90.2, C92.2, C93.1, C94.2, C96.1, R15.2, R16.2, R17.2, U14.2 (GND), U15.2 (GND), U16.2 (GND), U17.13 (GND), U17.18 (GND), U17.32 (VDD3), VDD3.1 (1_1); also elsewhere on the board
